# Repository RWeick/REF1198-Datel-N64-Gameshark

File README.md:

# REF1198-Datel-N64-Gameshark
The Kicad files for the Datel N64 Gameshark REF1198 PCB.

The edge connector spacing has been corrected from Datel's 2.54 mm to the N64 spec of 2.5 mm.

PCB Thickness: 1.2 mm

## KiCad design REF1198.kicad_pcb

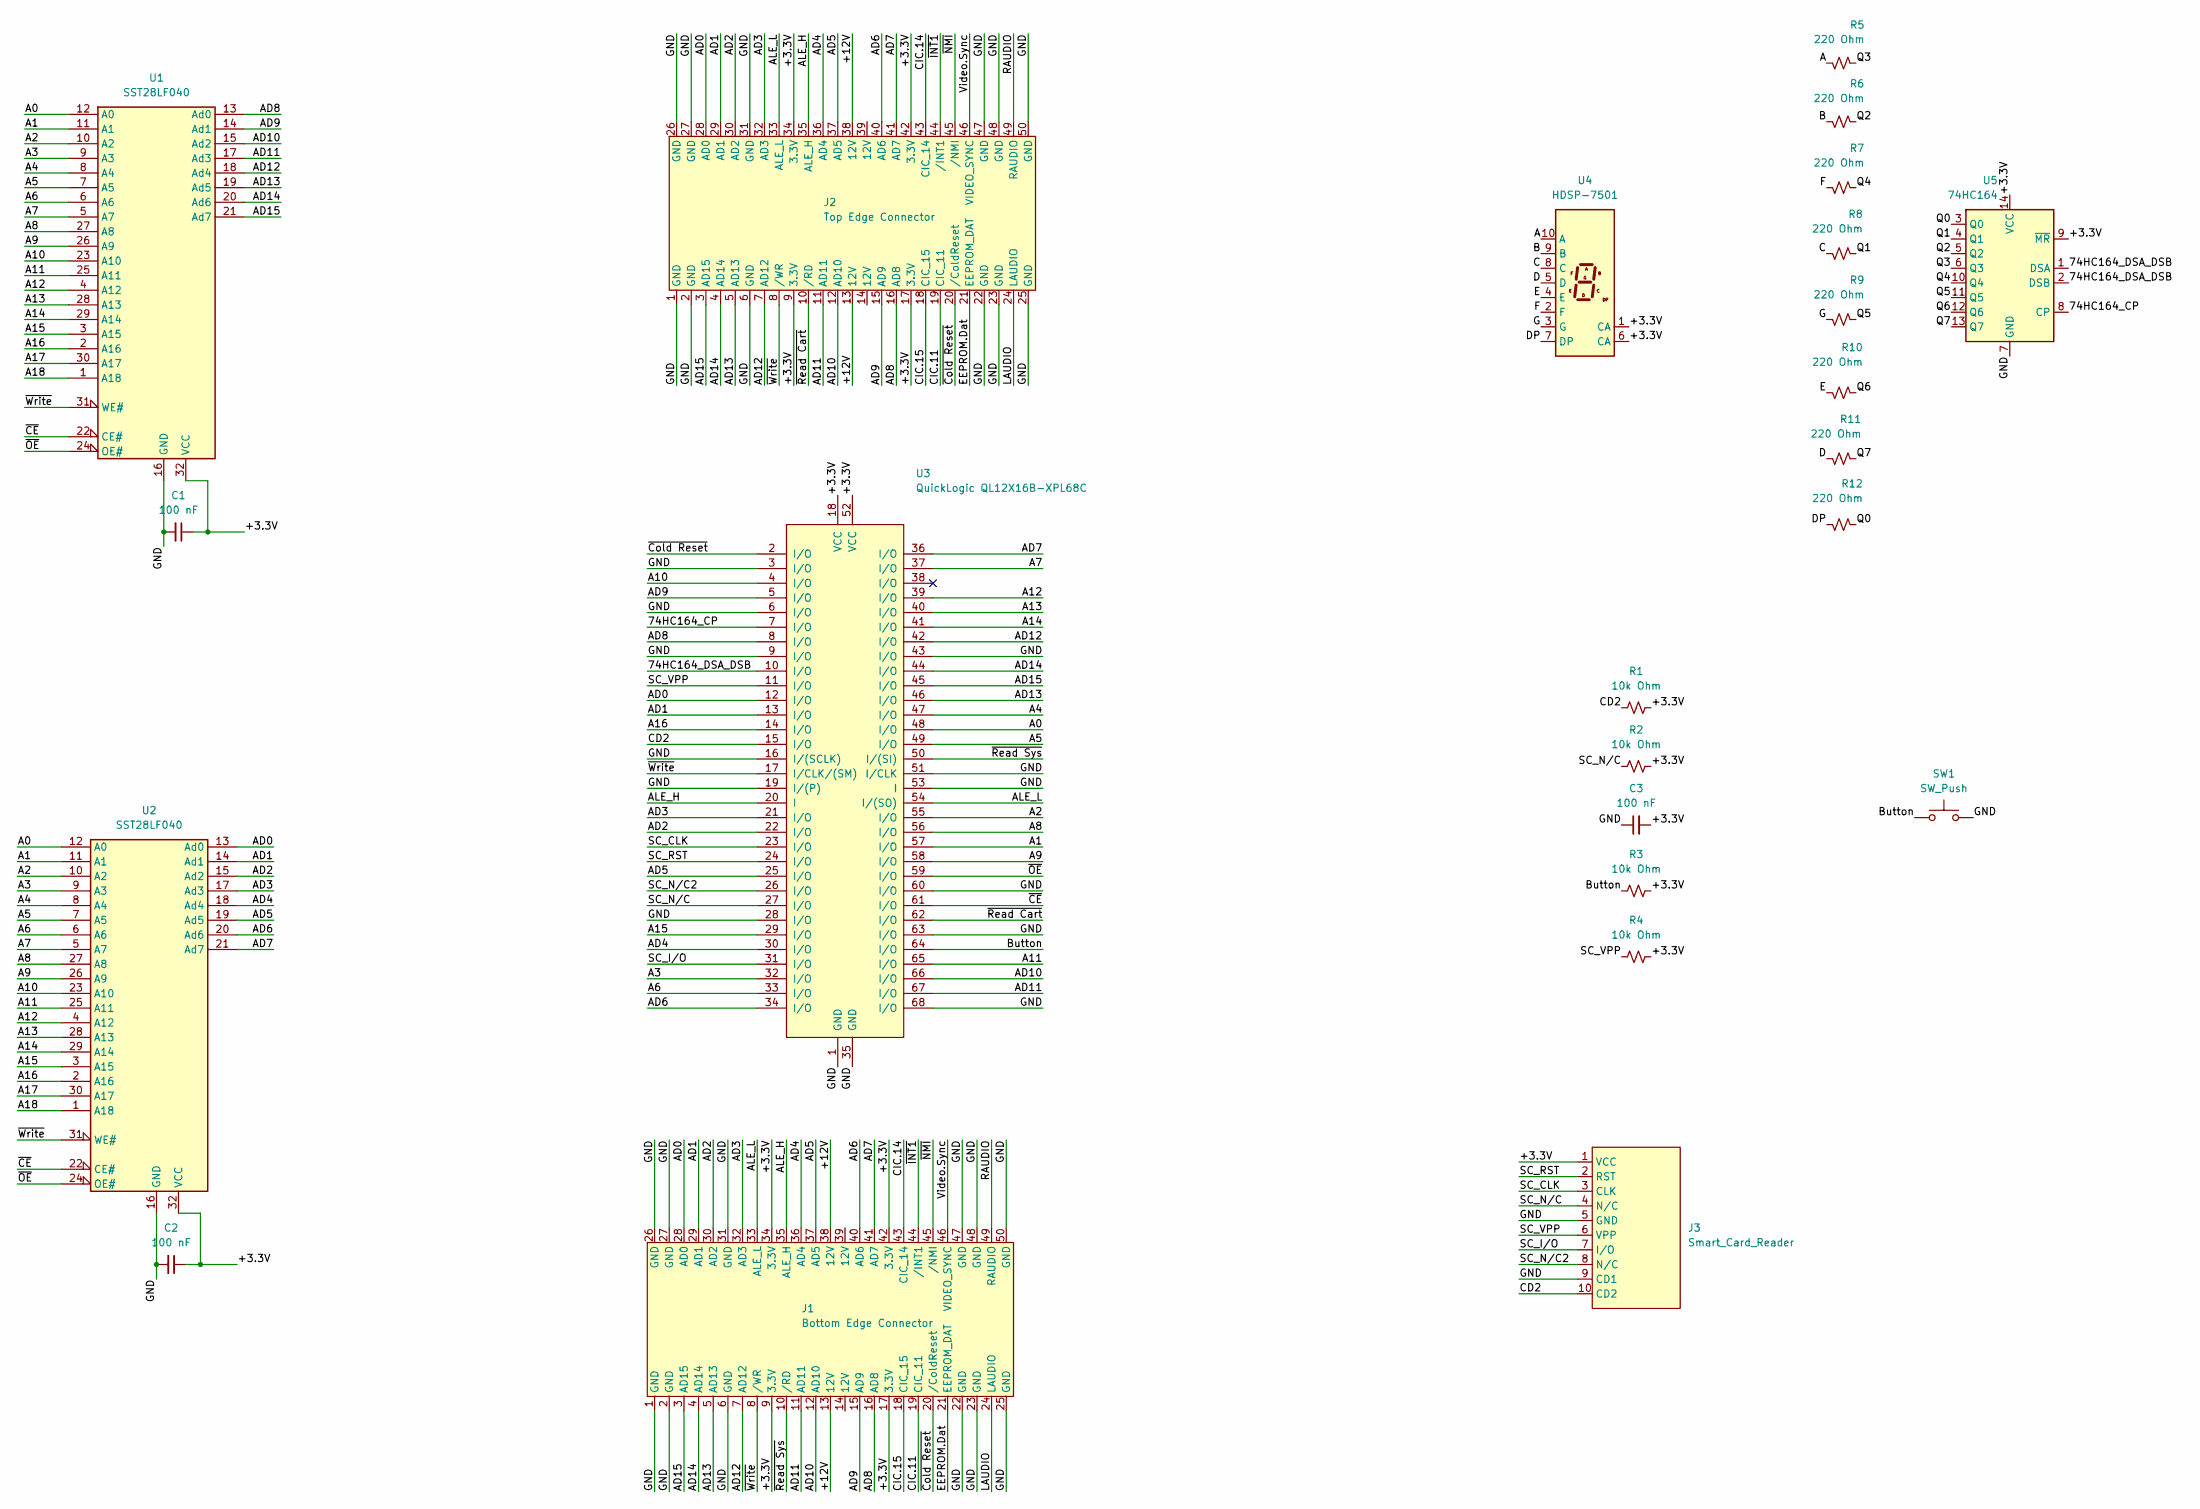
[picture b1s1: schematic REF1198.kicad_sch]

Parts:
C1, C2, C3: 100 nF; 1206 Cap Res
J1: Bottom Edge Connector; Edge Connector
J2: Top Edge Connector; Edge Connector
J3: Smart_Card_Reader; Smart Card Port
R1, R2, R3, R4: 10k Ohm; 1206 Cap Res
R5, R6, R7, R8, R9, R10, R11, R12: 220 Ohm; 0805 Res
SW1: SW_Push; Button
U1, U2: SST28LF040; EEPROM
U3: QuickLogic QL12X16B-XPL68C; QFP-68_24x24_Pitch1.27mm
U4: HDSP-7501
U5: 74HC164

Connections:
/74HC164_CP: U3.7 (I/O), U5.8 (CP)
/74HC164_DSA_DSB: U3.10 (I/O), U5.1 (DSA), U5.2 (DSB)
/+3.3V: C1.1, C2.1, C3.2, J1.9 (3.3V), J1.17 (3.3V), J1.34 (3.3V), J1.42 (3.3V), J2.9 (3.3V), J2.17 (3.3V), J2.34 (3.3V), J2.42 (3.3V), J3.1 (VCC), R1.2, R2.2, R3.2, R4.2, U1.32 (VCC), U2.32 (VCC), U3.18 (VCC), U3.52 (VCC), U4.1 (CA), U4.6 (CA), U5.9 (~MR), U5.14 (VCC)
/+12V: J1.13 (12V), J1.38 (12V), J2.13 (12V), J2.38 (12V)
/A: R5.1, U4.10 (A)
/A0: U1.12 (A0), U2.12 (A0), U3.48 (I/O)
/A1: U1.11 (A1), U2.11 (A1), U3.57 (I/O)
/A2: U1.10 (A2), U2.10 (A2), U3.55 (I/O)
/A3: U1.9 (A3), U2.9 (A3), U3.32 (I/O)
/A4: U1.8 (A4), U2.8 (A4), U3.47 (I/O)
/A5: U1.7 (A5), U2.7 (A5), U3.49 (I/O)
/A6: U1.6 (A6), U2.6 (A6), U3.33 (I/O)
/A7: U1.5 (A7), U2.5 (A7), U3.37 (I/O)
/A8: U1.27 (A8), U2.27 (A8), U3.56 (I/O)
/A9: U1.26 (A9), U2.26 (A9), U3.58 (I/O)
/A10: U1.23 (A10), U2.23 (A10), U3.4 (I/O)
/A11: U1.25 (A11), U2.25 (A11), U3.65 (I/O)
/A12: U1.4 (A12), U2.4 (A12), U3.39 (I/O)
/A13: U1.28 (A13), U2.28 (A13), U3.40 (I/O)
/A14: U1.29 (A14), U2.29 (A14), U3.41 (I/O)
/A15: U1.3 (A15), U2.3 (A15), U3.29 (I/O)
/A16: U1.2 (A16), U2.2 (A16), U3.14 (I/O)
/A17: U1.30 (A17), U2.30 (A17)
/A18: U1.1 (A18), U2.1 (A18)
/AD0: J1.28 (AD0), J2.28 (AD0), U2.13 (Ad0), U3.12 (I/O)
/AD1: J1.29 (AD1), J2.29 (AD1), U2.14 (Ad1), U3.13 (I/O)
/AD2: J1.30 (AD2), J2.30 (AD2), U2.15 (Ad2), U3.22 (I/O)
/AD3: J1.32 (AD3), J2.32 (AD3), U2.17 (Ad3), U3.21 (I/O)
/AD4: J1.36 (AD4), J2.36 (AD4), U2.18 (Ad4), U3.30 (I/O)
/AD5: J1.37 (AD5), J2.37 (AD5), U2.19 (Ad5), U3.25 (I/O)
/AD6: J1.40 (AD6), J2.40 (AD6), U2.20 (Ad6), U3.34 (I/O)
/AD7: J1.41 (AD7), J2.41 (AD7), U2.21 (Ad7), U3.36 (I/O)
/AD8: J1.16 (AD8), J2.16 (AD8), U1.13 (Ad0), U3.8 (I/O)
/AD9: J1.15 (AD9), J2.15 (AD9), U1.14 (Ad1), U3.5 (I/O)
/AD10: J1.12 (AD10), J2.12 (AD10), U1.15 (Ad2), U3.66 (I/O)
/AD11: J1.11 (AD11), J2.11 (AD11), U1.17 (Ad3), U3.67 (I/O)
/AD12: J1.7 (AD12), J2.7 (AD12), U1.18 (Ad4), U3.42 (I/O)
/AD13: J1.5 (AD13), J2.5 (AD13), U1.19 (Ad5), U3.46 (I/O)
/AD14: J1.4 (AD14), J2.4 (AD14), U1.20 (Ad6), U3.44 (I/O)
/AD15: J1.3 (AD15), J2.3 (AD15), U1.21 (Ad7), U3.45 (I/O)
/ALE_H: J1.35 (ALE_H), J2.35 (ALE_H), U3.20 (I)
/ALE_L: J1.33 (ALE_L), J2.33 (ALE_L), U3.54 (I/(SO))
/B: R6.1, U4.9 (B)
/Button: R3.1, SW1.1, U3.64 (I/O)
/C: R8.1, U4.8 (C)
/CD2: J3.10 (CD2), R1.1, U3.15 (I/O)
/CIC.11: J1.19 (CIC_11), J2.19 (CIC_11)
/CIC.14: J1.43 (CIC_14), J2.43 (CIC_14)
/CIC.15: J1.18 (CIC_15), J2.18 (CIC_15)
/D: R11.1, U4.5 (D)
/DP: R12.1, U4.7 (DP)
/E: R10.1, U4.4 (E)
/EEPROM.Dat: J1.21 (EEPROM_DAT), J2.21 (EEPROM_DAT)
/F: R7.1, U4.2 (F)
/G: R9.1, U4.3 (G)
/GND: C1.2, C2.2, C3.1, J1.1 (GND), J1.2 (GND), J1.6 (GND), J1.22 (GND), J1.23 (GND), J1.25 (GND), J1.26 (GND), J1.27 (GND), J1.31 (GND), J1.47 (GND), J1.48 (GND), J1.50 (GND), J2.1 (GND), J2.2 (GND), J2.6 (GND), J2.22 (GND), J2.23 (GND), J2.25 (GND), J2.26 (GND), J2.27 (GND), J2.31 (GND), J2.47 (GND), J2.48 (GND), J2.50 (GND), J3.5 (GND), J3.9 (CD1), SW1.2, U1.16 (GND), U2.16 (GND), U3.1 (GND), U3.3 (I/O), U3.6 (I/O), U3.9 (I/O), U3.16 (I/(SCLK)), U3.19 (I/(P)), U3.28 (I/O), U3.35 (GND), U3.43 (I/O), U3.51 (I/CLK), U3.53 (I), U3.60 (I/O), U3.63 (I/O), U3.68 (I/O), U5.7 (GND)
/LAUDIO: J1.24 (LAUDIO), J2.24 (LAUDIO)
/Q0: R12.2, U5.3 (Q0)
/Q1: R8.2, U5.4 (Q1)
/Q2: R6.2, U5.5 (Q2)
/Q3: R5.2, U5.6 (Q3)
/Q4: R7.2, U5.10 (Q4)
/Q5: R9.2, U5.11 (Q5)
/Q6: R10.2, U5.12 (Q6)
/Q7: R11.2, U5.13 (Q7)
/RAUDIO: J1.49 (RAUDIO), J2.49 (RAUDIO)
/SC_CLK: J3.3 (CLK), U3.23 (I/O)
/SC_I/O: J3.7 (I/O), U3.31 (I/O)
/SC_N/C: J3.4 (N/C), R2.1, U3.27 (I/O)
/SC_N/C2: J3.8 (N/C), U3.26 (I/O)
/SC_RST: J3.2 (RST), U3.24 (I/O)
/SC_VPP: J3.6 (VPP), R4.1, U3.11 (I/O)
/Video.Sync: J1.46 (VIDEO_SYNC), J2.46 (VIDEO_SYNC)
/~CE: U1.22 (CE#), U2.22 (CE#), U3.61 (I/O)
/~Cold Reset: J1.20 (/ColdReset), J2.20 (/ColdReset), U3.2 (I/O)
/~INT1: J1.44 (/INT1), J2.44 (/INT1)
/~NMI: J1.45 (/NMI), J2.45 (/NMI)
/~OE: U1.24 (OE#), U2.24 (OE#), U3.59 (I/O)
/~Read Cart: J2.10 (/RD), U3.62 (I/O)
/~Read Sys: J1.10 (/RD), U3.50 (I/(SI))
/~Write: J1.8 (/WR), J2.8 (/WR), U1.31 (WE#), U2.31 (WE#), U3.17 (I/CLK/(SM))

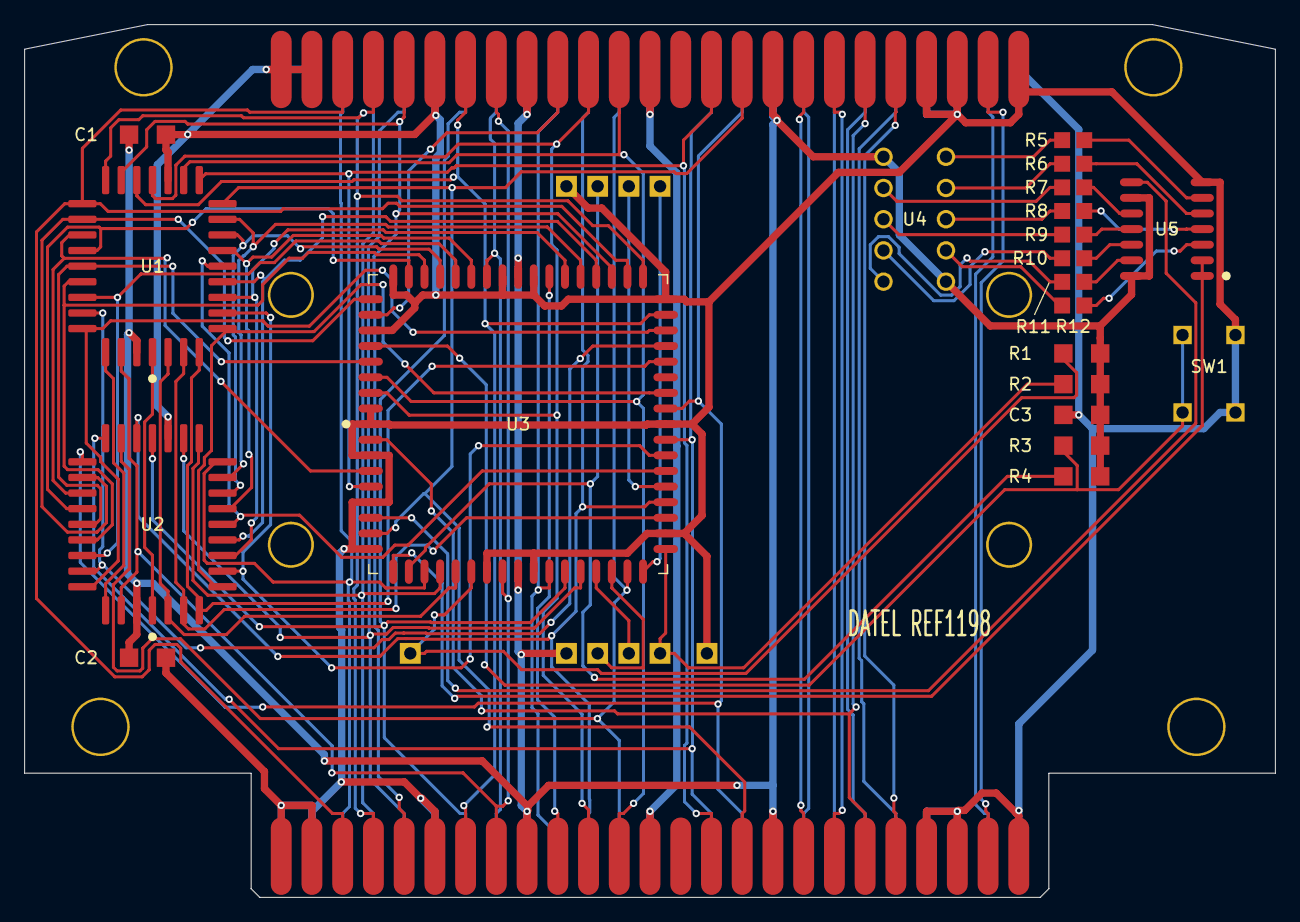
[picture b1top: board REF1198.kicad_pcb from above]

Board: 2 copper layers, 101.8 x 71.0 mm, 25 parts (0 on the bottom side), 81 nets.

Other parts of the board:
Holes: Drill Holes
